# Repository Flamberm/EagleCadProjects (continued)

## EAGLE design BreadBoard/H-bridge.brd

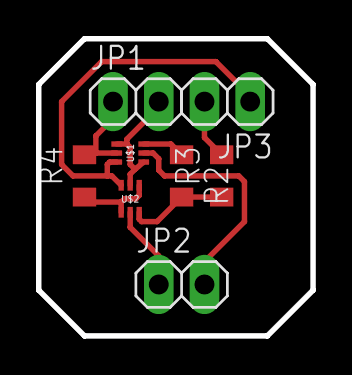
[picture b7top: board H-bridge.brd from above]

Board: 2 copper layers, 15.2 x 16.5 mm, 8 parts (0 on the bottom side), 9 nets.

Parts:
JP1, JP2, JP3: 1X02
R2, R3, R4: 0; R0805
U$1, U$2: FET-N/PNTZD3155C; SOT-563

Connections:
GND: JP3.1, U$1.6, U$2.6
unnamed: R4.1, U$2.1, U$2.4
unnamed: JP1.2, U$1.1, U$1.4, U$2.5
unnamed: JP2.1, U$2.2
unnamed: R2.1, U$1.3
unnamed: R2.2, R3.1, U$2.3
unnamed: JP1.1, R4.2, U$1.5
unnamed: JP2.2, U$1.2
VCC: JP3.2, R3.2

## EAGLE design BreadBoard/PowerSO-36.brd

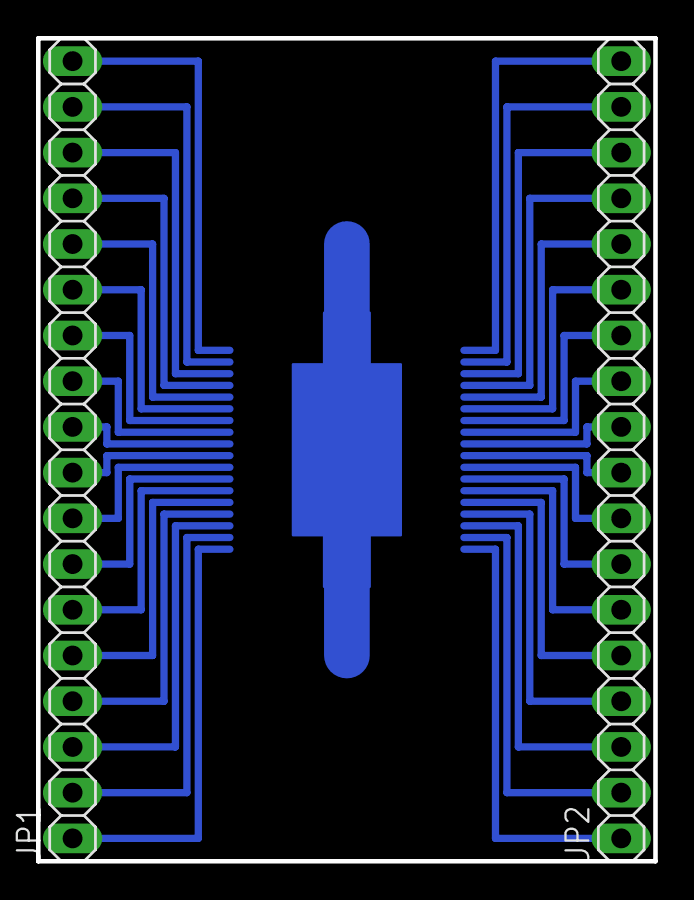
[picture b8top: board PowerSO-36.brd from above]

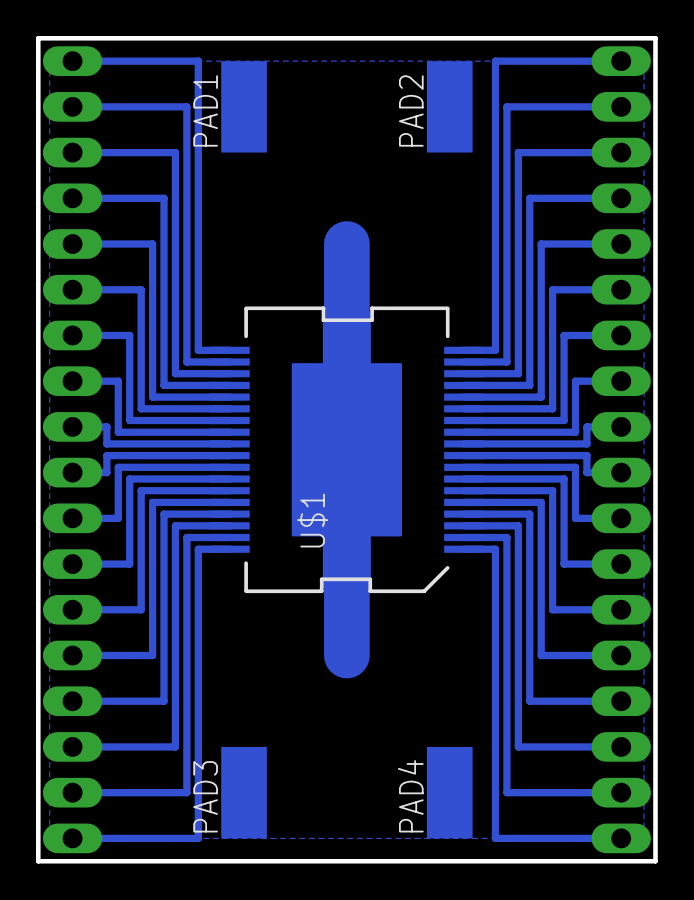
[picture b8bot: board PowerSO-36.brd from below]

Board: 2 copper layers, 34.3 x 45.7 mm, 7 parts (5 on the bottom side), 37 nets.

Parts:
JP1, JP2: 1X18
PAD1, PAD2, PAD3, PAD4: SMD2,54-5,08
U$1: POWERSO36; POWERSO-36

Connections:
unnamed: JP1.1, U$1.1
unnamed: JP1.2, U$1.2
unnamed: JP1.3, U$1.3
unnamed: JP1.4, U$1.4
unnamed: JP1.5, U$1.5
unnamed: JP1.6, U$1.6
unnamed: JP1.7, U$1.7
unnamed: JP1.8, U$1.8
unnamed: JP1.9, U$1.9
unnamed: JP1.10, U$1.10
unnamed: JP1.11, U$1.11
unnamed: JP1.12, U$1.12
unnamed: JP1.13, U$1.13
unnamed: JP1.14, U$1.14
unnamed: JP1.15, U$1.15
unnamed: JP1.16, U$1.16
unnamed: JP1.17, U$1.17
unnamed: JP1.18, U$1.18
unnamed: JP2.1, U$1.36
unnamed: JP2.2, U$1.35
unnamed: JP2.3, U$1.34
unnamed: JP2.4, U$1.33
unnamed: JP2.5, U$1.32
unnamed: JP2.6, U$1.31
unnamed: JP2.7, U$1.30
unnamed: JP2.8, U$1.29
unnamed: JP2.9, U$1.28
unnamed: JP2.10, U$1.27
unnamed: JP2.11, U$1.26
unnamed: JP2.12, U$1.25
unnamed: JP2.13, U$1.24
unnamed: JP2.14, U$1.23
unnamed: JP2.15, U$1.22
unnamed: JP2.16, U$1.21
unnamed: JP2.17, U$1.20
unnamed: JP2.18, U$1.19
unnamed: PAD1.1, PAD2.1, PAD3.1, PAD4.1
